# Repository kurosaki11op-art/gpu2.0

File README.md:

---
title: L second brain (home)
tags: [L, index]
---

# L: home

The team's second brain for L (PALS innoWAH! 2026-27). Everything about the project is written here, in
markdown, and opened in Obsidian as a vault or read on GitHub. Start at the top.

## Start here

> **Naming (22 Oct 2026):** the project is now called **L** (it was SPARK). Two workstreams: **L Cortex** (the counting chip, bit-exact RTL) and the **L accelerator** (a dedicated chip for the L language model, a GPU alternative: [design review](docs/L_accelerator_design.md)). Code, board and file names keep the old `spark_` prefix.

- [Overnight report, 15 Oct](docs/overnight_report_2026-10-15.md): what was done overnight and what to do with the board today.
- [Project memory](docs/PROJECT_MEMORY.md): identity, the user's standing rules, full history, current design, all results, plan. Read first.
- [Month 4 board plan](docs/month4_board_plan.md): what to run on the Tang Nano and how to read the power meter.
- [Claims sheet](docs/cortex_claims_sheet.md): what we can and cannot claim, with sources.
- [Results at a glance](docs/results_at_a_glance.md): the headline results, costs and limits on one page.
- [Journal](docs/journal.md): every step, newest at the bottom.
- [Session instructions](CLAUDE.md): how every working session must read and update this second brain.

## Current design: L Cortex

- [L Cortex redesign and 6-8 month plan](docs/cortex_redesign.md): what the chip is and the monthly proofs.
- [Brain code](hw/brain/README.md): the simulator for every part of the brain core.
- [Month 3 results](hw/results/cortex_month3.md): chip design bit-exact, bitstream for the Tang Nano, demo.
- [L Cortex vs HDC](hw/results/cortex_vs_hdc.md): against the closest prior art.
- [Month 2 results](hw/results/cortex_month2.md): memory shrunk to chip size, one rule, chip design bit-exact.
- [Month 2 running log](hw/results/cortex_month2_log.md): every test, including failures.
- [Month 1 results](hw/results/cortex_month1.md): accuracy gap closed.
- [First proof](hw/results/cortex_proof.md): no forgetting, exact merging.

## Indexes

- [Docs index](docs/INDEX.md): research, decisions, earlier architectures, pitch material.
- [Results index](hw/results/INDEX.md): every result, grouped by phase, with its label.
- [Hardware index](hw/HARDWARE_INDEX.md): RTL, board, ASIC, PCB, floorplan notes.
- [Prompts index](prompts/INDEX.md): prompts written for outside tools.

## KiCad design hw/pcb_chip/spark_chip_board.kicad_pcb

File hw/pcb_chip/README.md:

# L chip evaluation board (KiCad 7) — v0.1

Board for the packaged SKY130 L chip (`hw/rtl/spark_chip.v`, QFN-32 package plan in `gen_symbol.py`).

- USB-C (J1) → AP2112K-3.3 (U3) → AP2112K-1.8 (U4) → **0.1 Ω shunt (RS1) → chip core rail VCCD**;
  INA219 (U5) measures the chip's own core current and voltage (I2C on J2).
- CH340C (U2) bridges USB to the chip UART (the same protocol the testbench uses).
- 27 MHz oscillator (Y1) → 22 Ω → CLK; RST_N with 10 k pull-up, 1 µF and a reset button (SW1).
- LEDs on READY / BUSY / TOK; J2 = ESP32 logger header (3V3, GND, SDA, SCL, TRIG, TOK); J3 = debug UART.
- 4× 100 nF + 10 µF on each supply at the chip; test points on VCCD, 3V3, GND, CLK.

| Check | Result |
|---|---|
| Schematic connectivity + rules (KiCad netlist export, `verify_sch.py`) | 163 pins, 43 nets, **0 errors** (one documented waiver: CH340C V3 tied to VCC at 3.3 V, per datasheet) |
| KiCad DRC (`run_drc.py`) | **0 errors, 0 warnings, 0 unconnected** |
| PCB ↔ schematic parity | 168 pads, **0 mismatches** |

60 × 46 mm, 2 layers, Freerouting + GND pours. Chip rails use 0.25 mm tracks to reach the 0.5 mm-pitch QFN pins.
Limits: the L chip package/pinout is our plan (the die pad ring is not designed yet); not manufactured or tested.

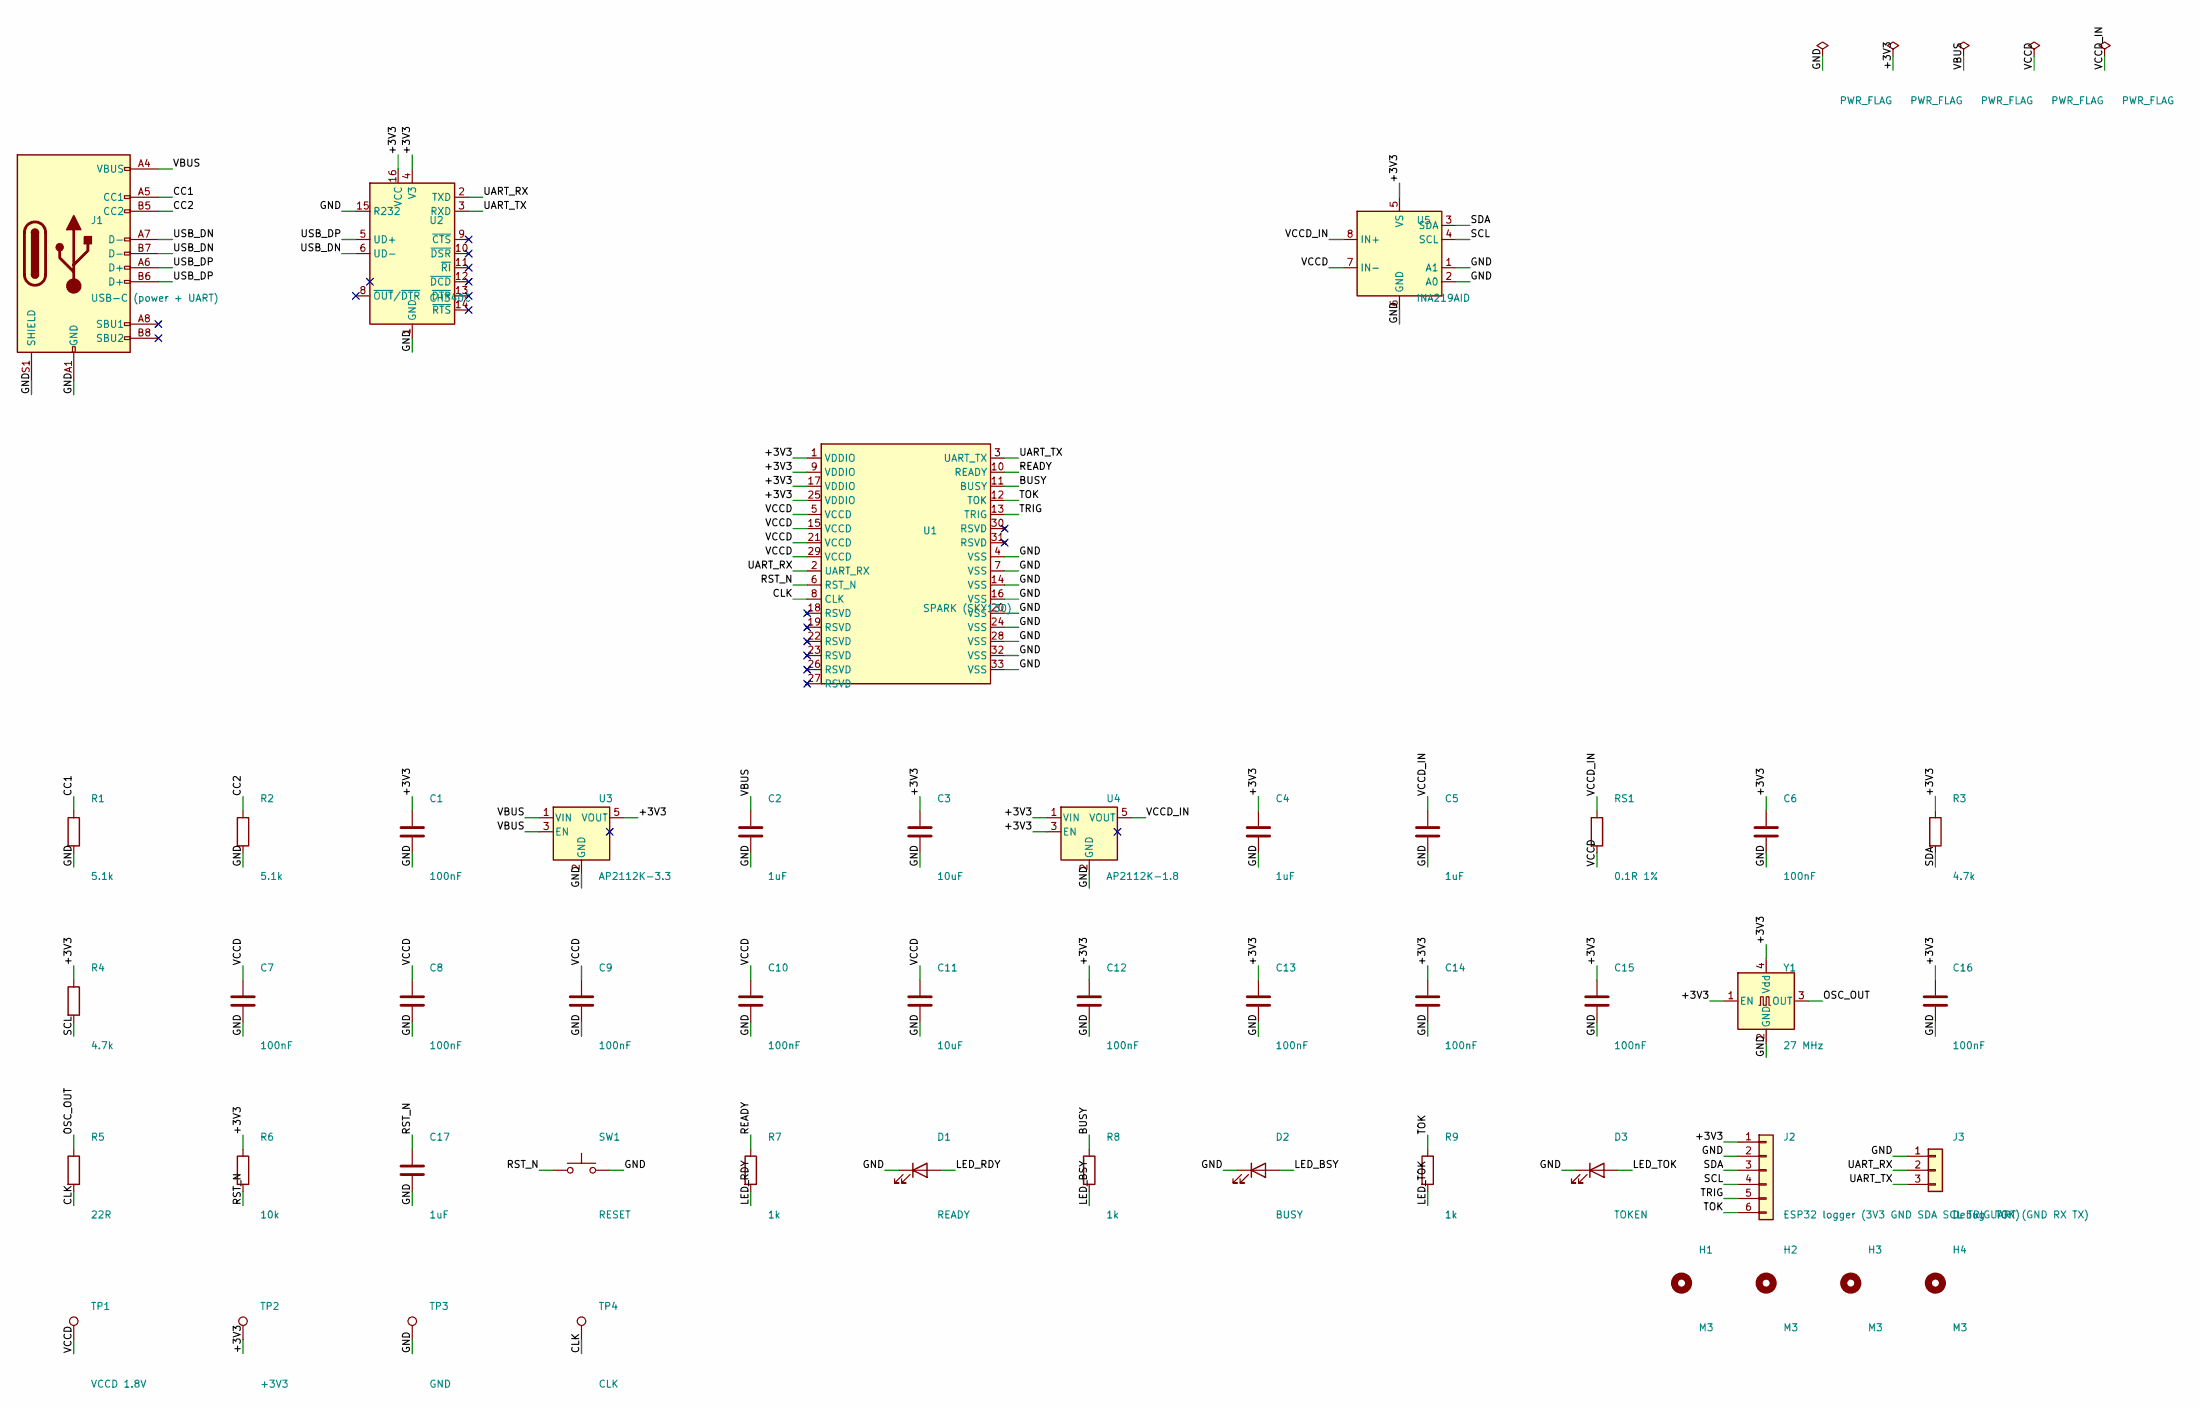
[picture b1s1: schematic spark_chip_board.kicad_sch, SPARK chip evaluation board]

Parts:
C1, C6, C7, C8, C9, C10, C12, C13, C14, C15, C16: 100nF; C_0603_1608Metric
C2, C4, C5, C17: 1uF; C_0603_1608Metric
C3, C11: 10uF; C_0805_2012Metric
D1: READY; LED_0603_1608Metric
D2: BUSY; LED_0603_1608Metric
D3: TOKEN; LED_0603_1608Metric
H1, H2, H3, H4: M3; MountingHole_3.2mm_M3
J1: USB-C (power + UART); USB_C_Receptacle_GCT_USB4105-xx-A_16P_TopMnt_Horizontal
J2: ESP32 logger (3V3 GND SDA SCL TRIG TOK); PinHeader_1x06_P2.54mm_Vertical
J3: Debug UART (GND RX TX); PinHeader_1x03_P2.54mm_Vertical
R1, R2: 5.1k; R_0603_1608Metric
R3, R4: 4.7k; R_0603_1608Metric
R5: 22R; R_0603_1608Metric
R6: 10k; R_0603_1608Metric
R7, R8, R9: 1k; R_0603_1608Metric
RS1: 0.1R 1%; R_1206_3216Metric
SW1: RESET; SW_SPST_PTS645
TP1: VCCD 1.8V; TestPoint_Pad_D1.5mm
TP2: +3V3; TestPoint_Pad_D1.5mm
TP3: GND; TestPoint_Pad_D1.5mm
TP4: CLK; TestPoint_Pad_D1.5mm
U1: SPARK (SKY130); QFN-32-1EP_5x5mm_P0.5mm_EP3.45x3.45mm
U2: CH340C; SOIC-16_3.9x9.9mm_P1.27mm
U3: AP2112K-3.3; SOT-23-5
U4: AP2112K-1.8; SOT-23-5
U5: INA219AID; SOIC-8_3.9x4.9mm_P1.27mm
Y1: 27 MHz; Oscillator_SMD_Abracon_ASE-4Pin_3.2x2.5mm

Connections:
+3V3: C1.1, C3.1, C4.1, C6.1, C12.1, C13.1, C14.1, C15.1, C16.1, J2.1, R3.1, R4.1, R6.1, TP2.1, U1.1 (VDDIO), U1.9 (VDDIO), U1.17 (VDDIO), U1.25 (VDDIO), U2.4 (V3), U2.16 (VCC), U3.5 (VOUT), U4.1 (VIN), U4.3 (EN), U5.5 (VS), Y1.1 (EN), Y1.4 (Vdd)
BUSY: R8.1, U1.11 (BUSY)
CC1: J1.A5 (CC1), R1.1
CC2: J1.B5 (CC2), R2.1
CLK: R5.2, TP4.1, U1.8 (CLK)
GND: C1.2, C2.2, C3.2, C4.2, C5.2, C6.2, C7.2, C8.2, C9.2, C10.2, C11.2, C12.2, C13.2, C14.2, C15.2, C16.2, C17.2, D1.1 (K), D2.1 (K), D3.1 (K), J1.A1 (GND), J1.A12 (GND), J1.B1 (GND), J1.B12 (GND), J1.S1 (SHIELD), J2.2, J3.1, R1.2, R2.2, SW1.2, TP3.1, U1.4 (VSS), U1.7 (VSS), U1.14 (VSS), U1.16 (VSS), U1.20 (VSS), U1.24 (VSS), U1.28 (VSS), U1.32 (VSS), U1.33 (VSS), U2.1 (GND), U2.15 (R232), U3.2 (GND), U4.2 (GND), U5.1 (A1), U5.2 (A0), U5.6 (GND), Y1.2 (GND)
LED_BSY: D2.2 (A), R8.2
LED_RDY: D1.2 (A), R7.2
LED_TOK: D3.2 (A), R9.2
OSC_OUT: R5.1, Y1.3 (OUT)
READY: R7.1, U1.10 (READY)
RST_N: C17.1, R6.2, SW1.1, U1.6 (RST_N)
SCL: J2.4, R4.2, U5.4 (SCL)
SDA: J2.3, R3.2, U5.3 (SDA)
TOK: J2.6, R9.1, U1.12 (TOK)
TRIG: J2.5, U1.13 (TRIG)
UART_RX: J3.2, U1.2 (UART_RX), U2.2 (TXD)
UART_TX: J3.3, U1.3 (UART_TX), U2.3 (RXD)
USB_DN: J1.A7 (D-), J1.B7 (D-), U2.6 (UD-)
USB_DP: J1.A6 (D+), J1.B6 (D+), U2.5 (UD+)
VBUS: C2.1, J1.A4 (VBUS), J1.A9 (VBUS), J1.B4 (VBUS), J1.B9 (VBUS), U3.1 (VIN), U3.3 (EN)
VCCD: C7.1, C8.1, C9.1, C10.1, C11.1, RS1.2, TP1.1, U1.5 (VCCD), U1.15 (VCCD), U1.21 (VCCD), U1.29 (VCCD), U5.7 (IN-)
VCCD_IN: C5.1, RS1.1, U4.5 (VOUT), U5.8 (IN+)

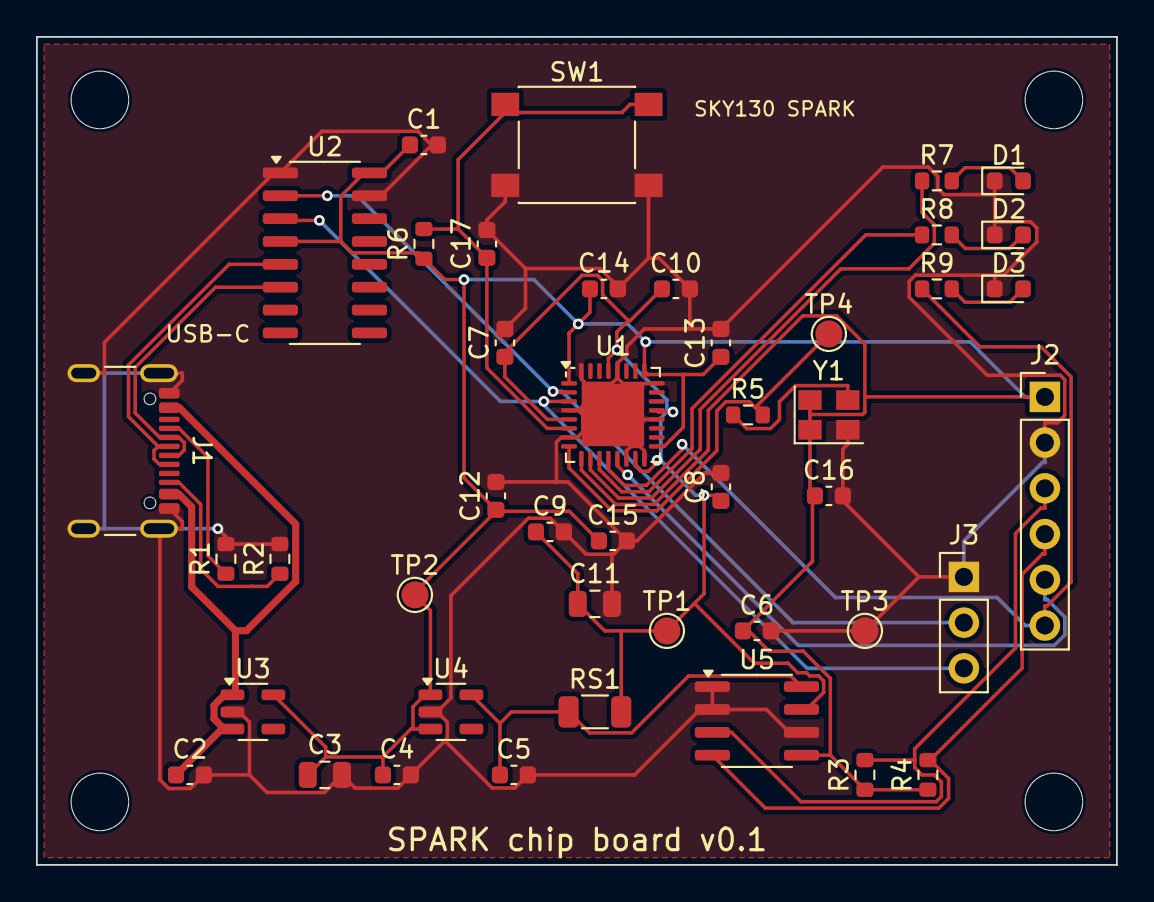
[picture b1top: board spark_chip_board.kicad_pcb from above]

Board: 2 copper layers, 60.0 x 46.0 mm, 48 parts (0 on the bottom side), 23 nets.

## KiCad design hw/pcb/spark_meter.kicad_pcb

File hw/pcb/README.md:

# L power-measurement board (KiCad 7) — v0.1

An inline USB-C power meter for the L FPGA prototype:
laptop USB-C (J1) → 0.1 Ω shunt (RS1) → USB-C (J2) → Sipeed Tang Nano 20K. USB 2.0 data passes straight through.
INA219 (U1) measures shunt current and bus voltage, LM75 (U2) board temperature, J5 takes a DS18B20 probe for the
FPGA package, J3 takes the FPGA's benchmark marker wire, and J4 connects any ESP32 board (3V3, GND, SDA, SCL, MARKER, DQ).
Powering the Tang Nano through its own USB-C port avoids any assumption about its header pinout.

| File | What |
|---|---|
| `design.py` | Single source of truth: parts, footprints, every pin → net |
| `make_sch.py` → `spark_meter.kicad_sch` | Schematic (official KiCad library symbols) |
| `make_pcb.py` → `spark_meter.kicad_pcb` | 2-layer 72 × 52 mm board, placement, Freerouting autoroute, GND pours |
| `verify_sch.py`, `run_drc.py` | Verification (below) |
| `fab/` | Gerbers, drill file, pick-and-place |
| `img/` | Schematic (PDF/SVG/PNG) and board renders |

## Verification (reproduce: `python3 make_sch.py && kicad-cli sch export netlist --format kicadsexpr -o spark_meter.net spark_meter.kicad_sch && python3 verify_sch.py && python3 make_pcb.py place && xvfb-run -a java -jar freerouting-1.9.0.jar -de spark_meter.dsn -do spark_meter.ses -mp 30 && python3 make_pcb.py finish && python3 run_drc.py`)
| Check | Tool | Result |
|---|---|---|
| Schematic connectivity: every pin on the intended net | netlist exported by KiCad from the schematic vs `design.py` | 92 pins, 15 nets + 5 intentional no-connects, **0 errors** (107 checks) |
| Electrical rules: single-pin nets, undriven power inputs, multiple drivers, undriven inputs | `verify_sch.py` (KiCad 7 CLI has no ERC) | **0 errors** |
| Design-rule check | KiCad DRC engine (`pcbnew.WriteDRCReport`) | **0 errors, 0 warnings, 0 unconnected** |
| PCB ↔ schematic parity | every PCB pad net vs KiCad's schematic netlist | 98 pads, **0 mismatches** |

Rules: 0.2 mm signal / 0.5 mm power tracks, 0.15 mm clearance, 0.6/0.3 mm vias, 0.3 mm copper-to-edge.
Hole clearance is set to 0.18 mm because the GCT USB4105 manufacturer land pattern places its locating pegs
0.194 mm from the GND pads; confirm with the PCB fab.

## Known limits before ordering (v0.2)
- The INA219 sense inputs connect through the VBUS nets, not dedicated Kelvin traces at the shunt pads
  (adds an error of roughly trace resistance / 100 mΩ, ~1–2 %).
- USB D+/D− are routed as plain tracks, not an impedance-controlled 90 Ω pair; fine for full speed, check for high speed.
- Not built or bench-tested yet. Component values follow the INA219 / LM75 datasheets' typical circuits.

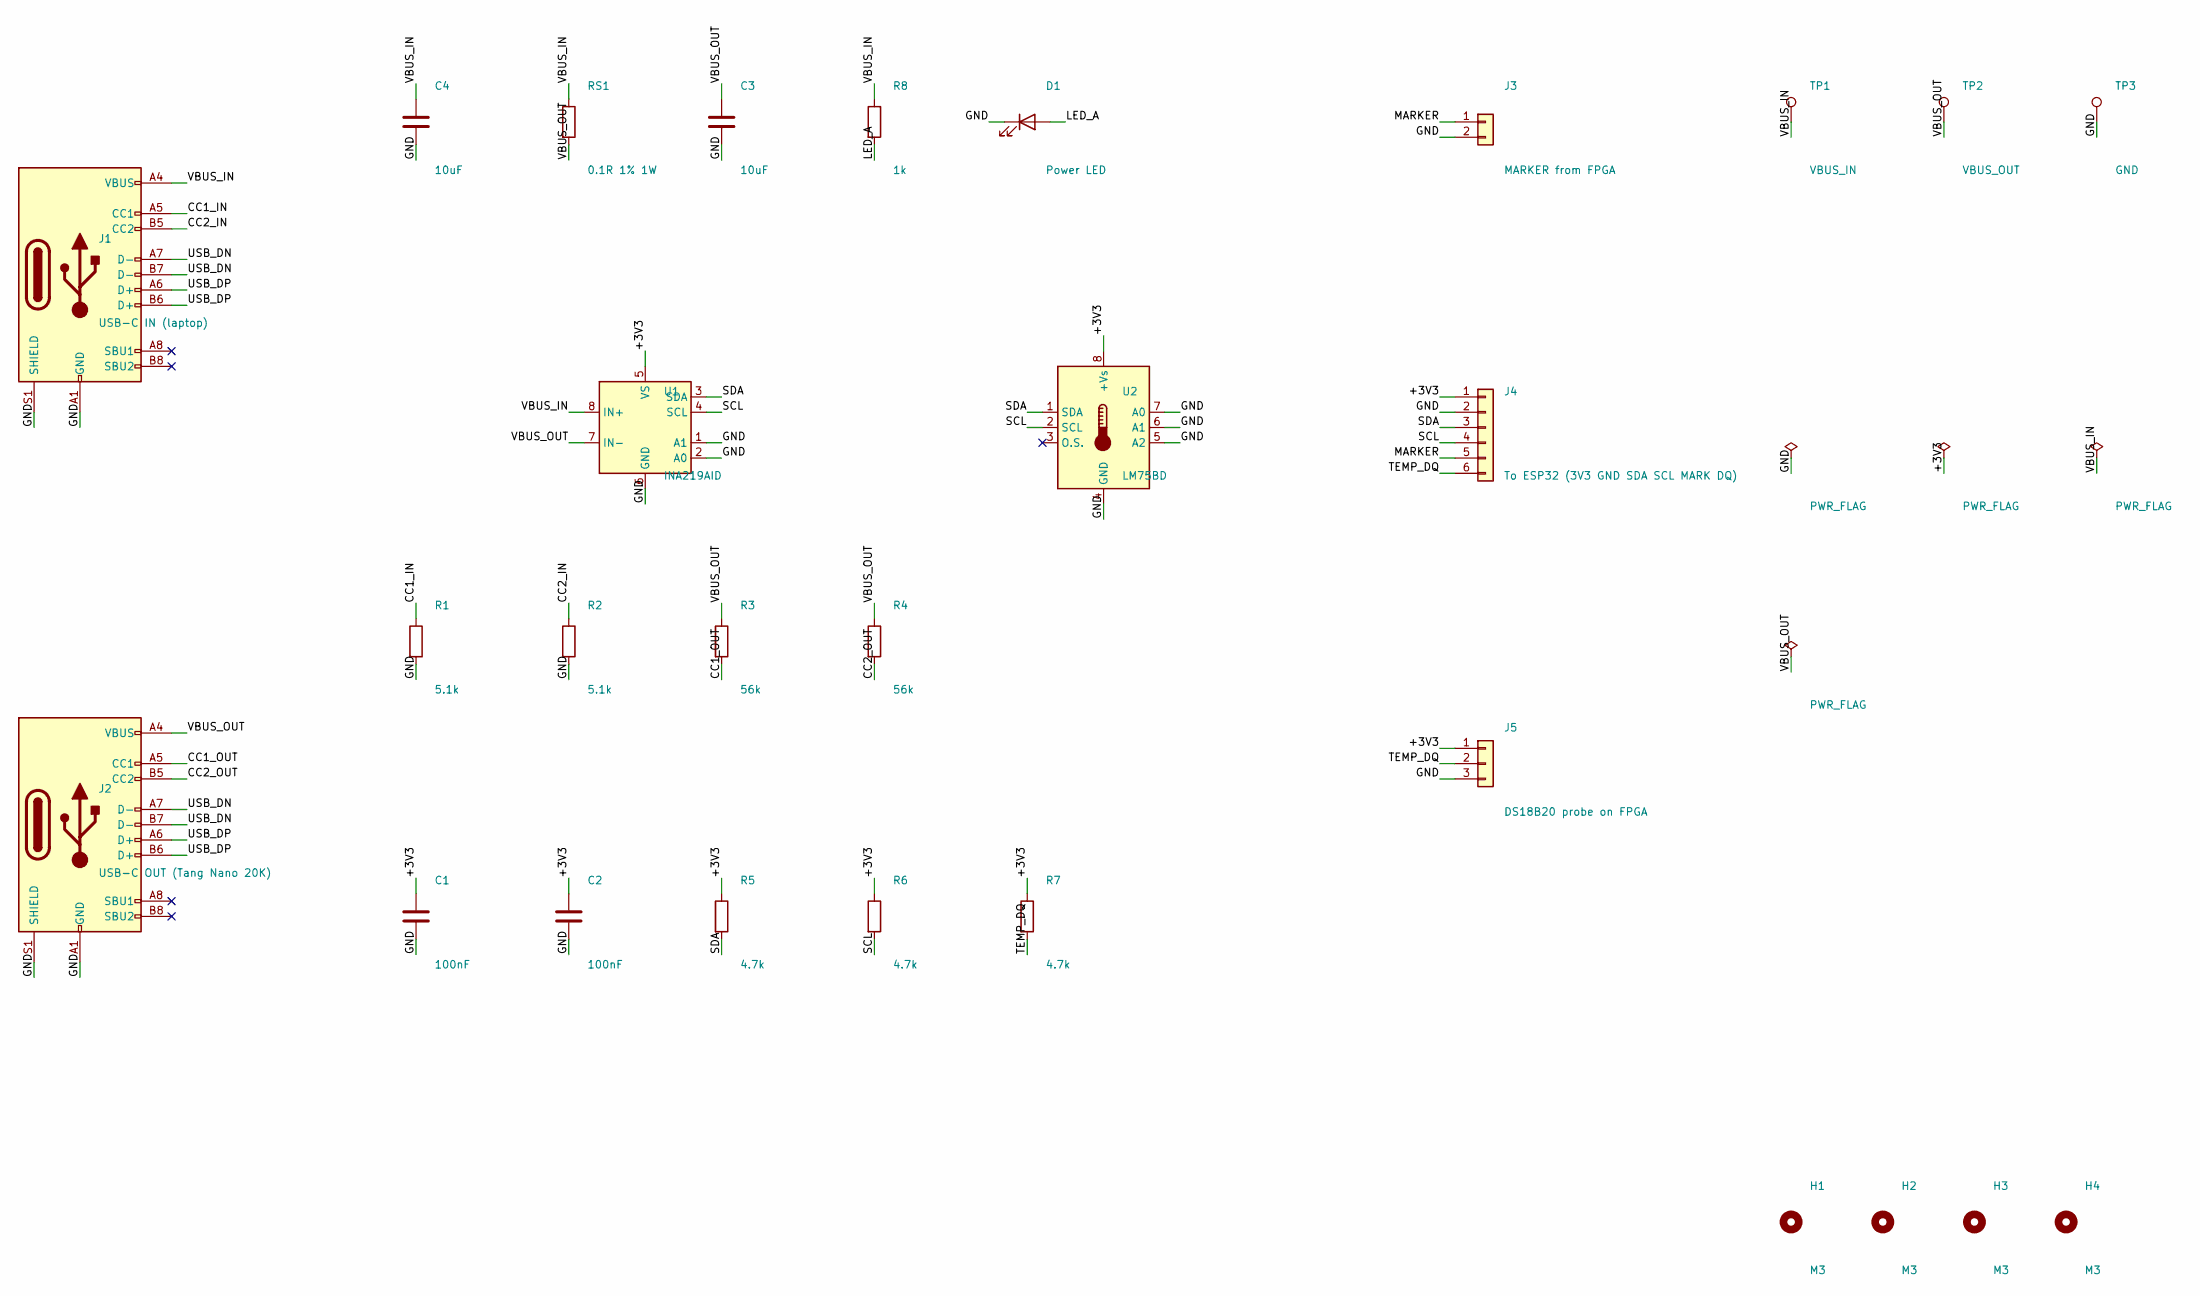
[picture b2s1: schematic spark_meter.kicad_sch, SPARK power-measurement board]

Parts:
C1, C2: 100nF; C_0603_1608Metric
C3, C4: 10uF; C_0805_2012Metric
D1: Power LED; LED_0603_1608Metric
H1, H2, H3, H4: M3; MountingHole_3.2mm_M3
J1: USB-C IN (laptop); USB_C_Receptacle_GCT_USB4105-xx-A_16P_TopMnt_Horizontal
J2: USB-C OUT (Tang Nano 20K); USB_C_Receptacle_GCT_USB4105-xx-A_16P_TopMnt_Horizontal
J3: MARKER from FPGA; PinHeader_1x02_P2.54mm_Vertical
J4: To ESP32 (3V3 GND SDA SCL MARK DQ); PinHeader_1x06_P2.54mm_Vertical
J5: DS18B20 probe on FPGA; PinHeader_1x03_P2.54mm_Vertical
R1, R2: 5.1k; R_0603_1608Metric
R3, R4: 56k; R_0603_1608Metric
R5, R6, R7: 4.7k; R_0603_1608Metric
R8: 1k; R_0603_1608Metric
RS1: 0.1R 1% 1W; R_2512_6332Metric
TP1: VBUS_IN; TestPoint_Pad_D1.5mm
TP2: VBUS_OUT; TestPoint_Pad_D1.5mm
TP3: GND; TestPoint_Pad_D1.5mm
U1: INA219AID; SOIC-8_3.9x4.9mm_P1.27mm
U2: LM75BD; SOIC-8_3.9x4.9mm_P1.27mm

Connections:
+3V3: C1.1, C2.1, J4.1, J5.1, R5.1, R6.1, R7.1, U1.5 (VS), U2.8 (+Vs)
CC1_IN: J1.A5 (CC1), R1.1
CC1_OUT: J2.A5 (CC1), R3.2
CC2_IN: J1.B5 (CC2), R2.1
CC2_OUT: J2.B5 (CC2), R4.2
GND: C1.2, C2.2, C3.2, C4.2, D1.1 (K), J1.A1 (GND), J1.A12 (GND), J1.B1 (GND), J1.B12 (GND), J1.S1 (SHIELD), J2.A1 (GND), J2.A12 (GND), J2.B1 (GND), J2.B12 (GND), J2.S1 (SHIELD), J3.2, J4.2, J5.3, R1.2, R2.2, TP3.1, U1.1 (A1), U1.2 (A0), U1.6 (GND), U2.4 (GND), U2.5 (A2), U2.6 (A1), U2.7 (A0)
LED_A: D1.2 (A), R8.2
MARKER: J3.1, J4.5
SCL: J4.4, R6.2, U1.4 (SCL), U2.2 (SCL)
SDA: J4.3, R5.2, U1.3 (SDA), U2.1 (SDA)
TEMP_DQ: J4.6, J5.2, R7.2
USB_DN: J1.A7 (D-), J1.B7 (D-), J2.A7 (D-), J2.B7 (D-)
USB_DP: J1.A6 (D+), J1.B6 (D+), J2.A6 (D+), J2.B6 (D+)
VBUS_IN: C4.1, J1.A4 (VBUS), J1.A9 (VBUS), J1.B4 (VBUS), J1.B9 (VBUS), R8.1, RS1.1, TP1.1, U1.8 (IN+)
VBUS_OUT: C3.1, J2.A4 (VBUS), J2.A9 (VBUS), J2.B4 (VBUS), J2.B9 (VBUS), R3.1, R4.1, RS1.2, TP2.1, U1.7 (IN-)

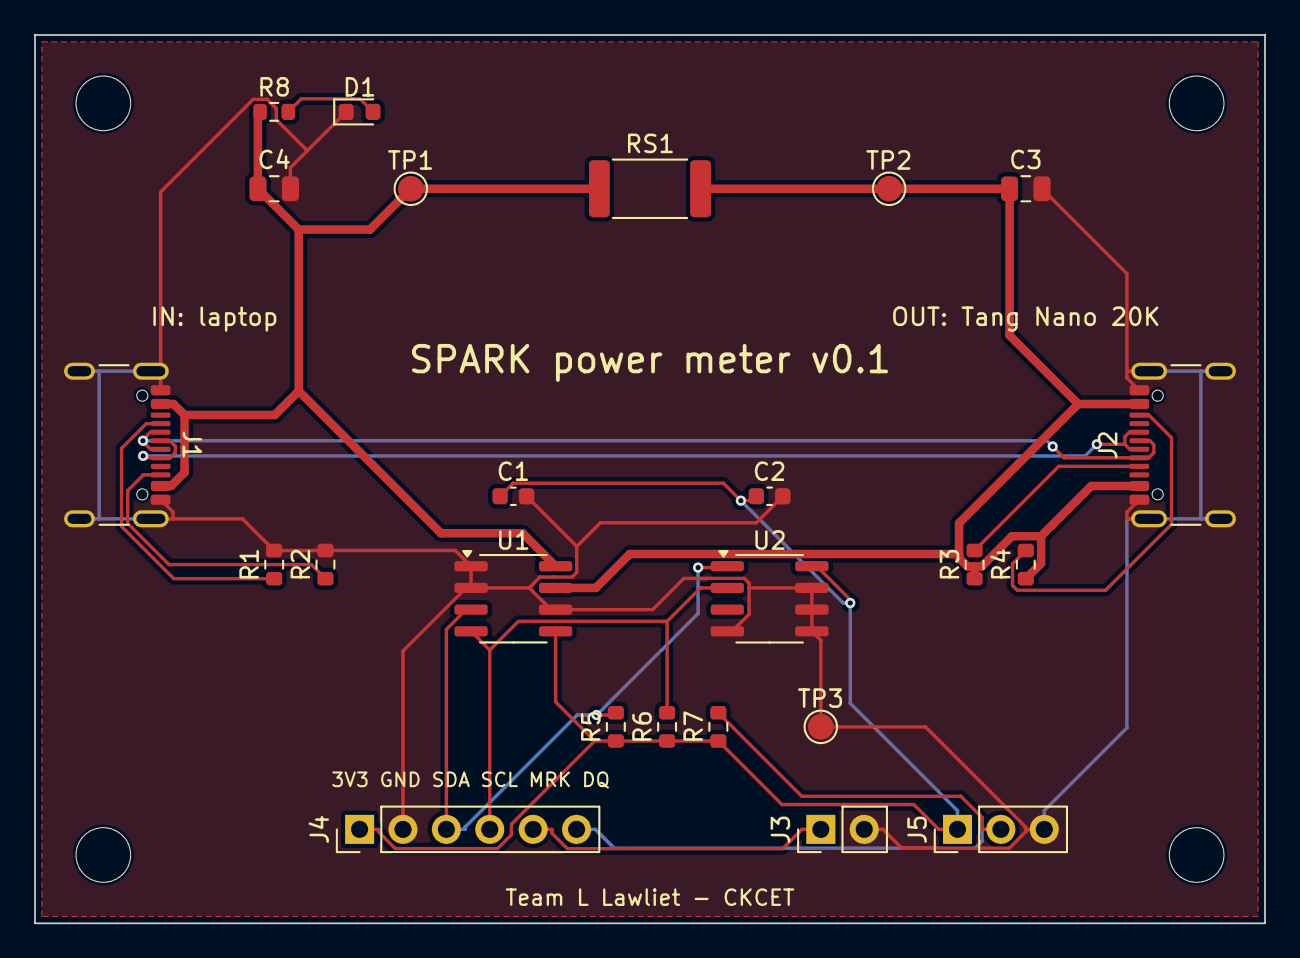
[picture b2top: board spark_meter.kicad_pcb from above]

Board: 2 copper layers, 72.0 x 52.0 mm, 28 parts (0 on the bottom side), 15 nets.
